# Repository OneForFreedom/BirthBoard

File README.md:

# BirthBoard
A 60% ISO keyboard that has an oled to count down the days to your birthday!

Images + Schematic:

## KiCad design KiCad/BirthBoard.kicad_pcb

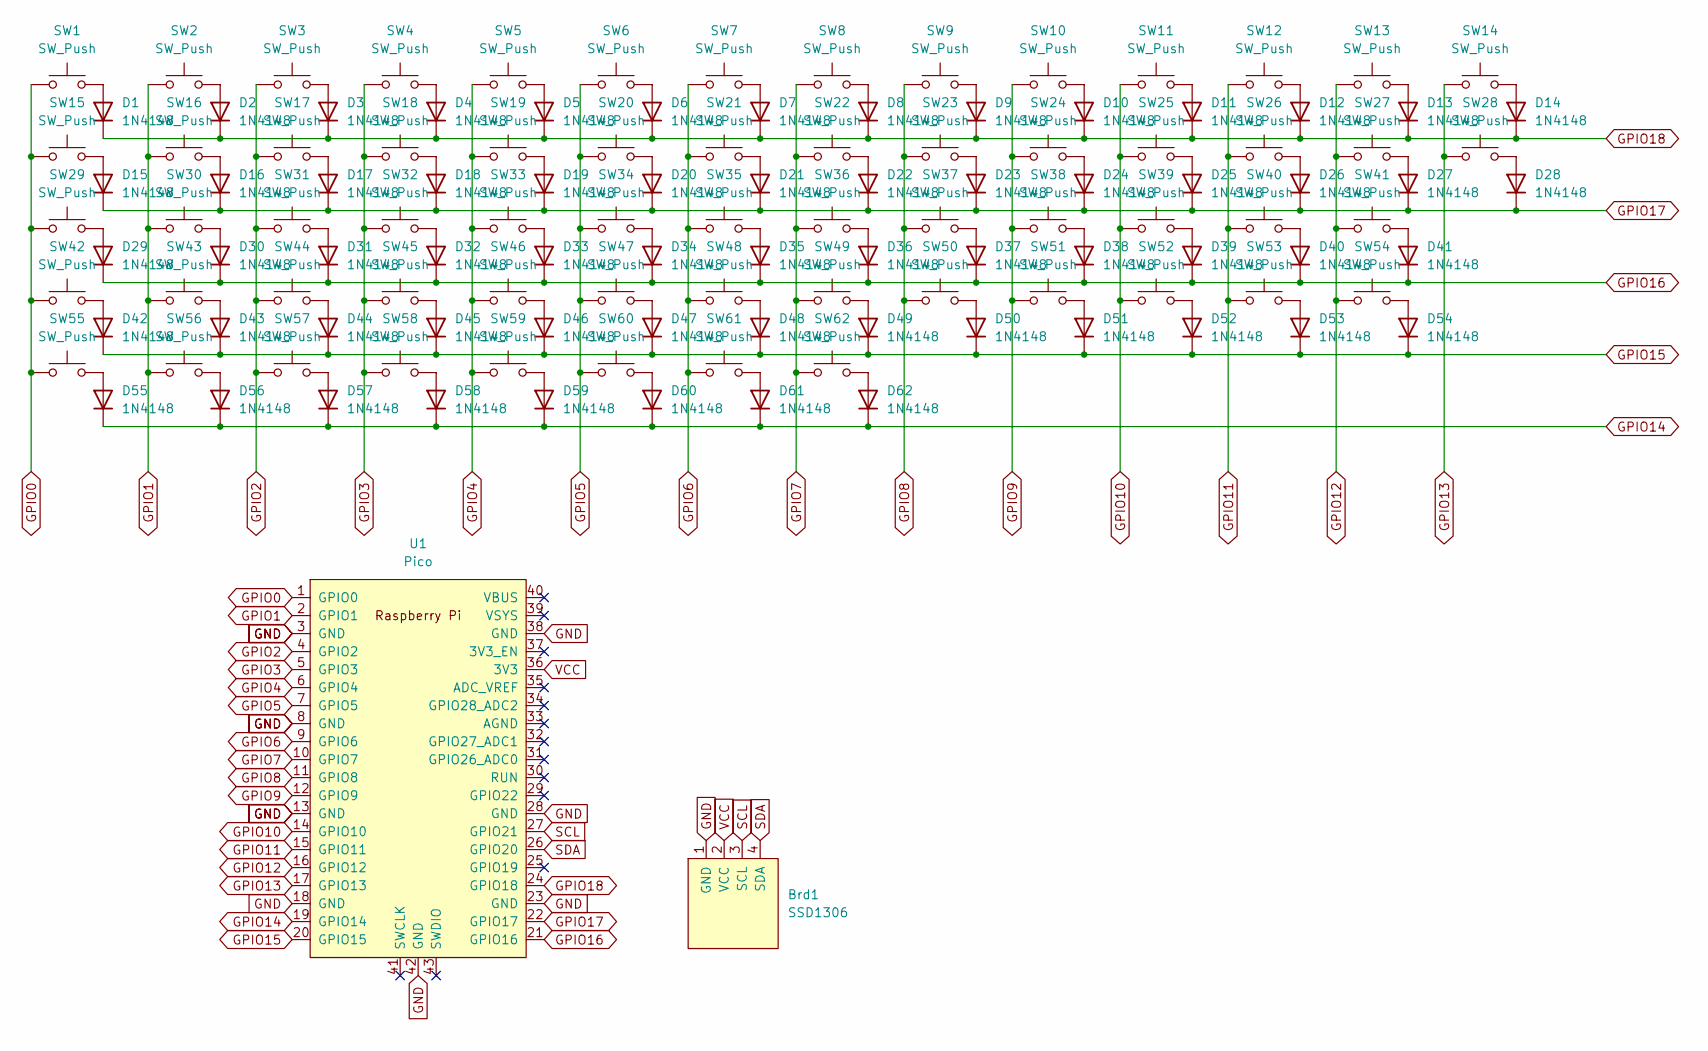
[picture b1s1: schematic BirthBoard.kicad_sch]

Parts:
Brd1: SSD1306; 128x64OLED
D1, D2, D3, D4, D5, D6, D7, D8, D9, D10, D11, D12, D13, D14, D15, D16, D17, D18, D19, D20, D21, D22, D23, D24, D25, D26, D27, D28, D29, D30, D31, D32, D33, D34, D35, D36, D37, D38, D39, D40, D41, D42, D43, D44, D45, D46, D47, D48, D49, D50, D51, D52, D53, D54, D55, D56, D57, D58, D59, D60, D61, D62: 1N4148; D_DO-35_SOD27_P7.62mm_Horizontal
SW1, SW2, SW3, SW4, SW5, SW6, SW7, SW8, SW9, SW10, SW11, SW12, SW13, SW14, SW15, SW16, SW17, SW18, SW19, SW20, SW21, SW22, SW23, SW24, SW25, SW26, SW27, SW28, SW29, SW30, SW31, SW32, SW33, SW34, SW35, SW36, SW37, SW38, SW39, SW40, SW41, SW42, SW43, SW44, SW45, SW46, SW47, SW48, SW49, SW50, SW51, SW52, SW53, SW54, SW55, SW56, SW57, SW58, SW59, SW60, SW61, SW62: SW_Push; SW_Cherry_MX_1.00u_PCB 1
U1: Pico; RPi_Pico_SMD_TH

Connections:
GND: Brd1.1 (GND), U1.3 (GND), U1.8 (GND), U1.13 (GND), U1.18 (GND), U1.23 (GND), U1.28 (GND), U1.38 (GND), U1.42 (GND)
GPIO0: SW1.1, SW15.1, SW29.1, SW42.1, SW55.1, U1.1 (GPIO0)
GPIO1: SW2.1, SW16.1, SW30.1, SW43.1, SW56.1, U1.2 (GPIO1)
GPIO2: SW3.1, SW17.1, SW31.1, SW44.1, SW57.1, U1.4 (GPIO2)
GPIO3: SW4.1, SW18.1, SW32.1, SW45.1, SW58.1, U1.5 (GPIO3)
GPIO4: SW5.1, SW19.1, SW33.1, SW46.1, SW59.1, U1.6 (GPIO4)
GPIO5: SW6.1, SW20.1, SW34.1, SW47.1, SW60.1, U1.7 (GPIO5)
GPIO6: SW7.1, SW21.1, SW35.1, SW48.1, SW61.1, U1.9 (GPIO6)
GPIO7: SW8.1, SW22.1, SW36.1, SW49.1, SW62.1, U1.10 (GPIO7)
GPIO8: SW9.1, SW23.1, SW37.1, SW50.1, U1.11 (GPIO8)
GPIO9: SW10.1, SW24.1, SW38.1, SW51.1, U1.12 (GPIO9)
GPIO10: SW11.1, SW25.1, SW39.1, SW52.1, U1.14 (GPIO10)
GPIO11: SW12.1, SW26.1, SW40.1, SW53.1, U1.15 (GPIO11)
GPIO12: SW13.1, SW27.1, SW41.1, SW54.1, U1.16 (GPIO12)
GPIO13: SW14.1, SW28.1, U1.17 (GPIO13)
GPIO14: D55.1 (K), D56.1 (K), D57.1 (K), D58.1 (K), D59.1 (K), D60.1 (K), D61.1 (K), D62.1 (K), U1.19 (GPIO14)
GPIO15: D42.1 (K), D43.1 (K), D44.1 (K), D45.1 (K), D46.1 (K), D47.1 (K), D48.1 (K), D49.1 (K), D50.1 (K), D51.1 (K), D52.1 (K), D53.1 (K), D54.1 (K), U1.20 (GPIO15)
GPIO16: D29.1 (K), D30.1 (K), D31.1 (K), D32.1 (K), D33.1 (K), D34.1 (K), D35.1 (K), D36.1 (K), D37.1 (K), D38.1 (K), D39.1 (K), D40.1 (K), D41.1 (K), U1.21 (GPIO16)
GPIO17: D15.1 (K), D16.1 (K), D17.1 (K), D18.1 (K), D19.1 (K), D20.1 (K), D21.1 (K), D22.1 (K), D23.1 (K), D24.1 (K), D25.1 (K), D26.1 (K), D27.1 (K), D28.1 (K), U1.22 (GPIO17)
GPIO18: D1.1 (K), D2.1 (K), D3.1 (K), D4.1 (K), D5.1 (K), D6.1 (K), D7.1 (K), D8.1 (K), D9.1 (K), D10.1 (K), D11.1 (K), D12.1 (K), D13.1 (K), D14.1 (K), U1.24 (GPIO18)
unnamed: D1.2 (A), SW1.2
unnamed: D2.2 (A), SW2.2
unnamed: D3.2 (A), SW3.2
unnamed: D4.2 (A), SW4.2
unnamed: D5.2 (A), SW5.2
unnamed: D6.2 (A), SW6.2
unnamed: D7.2 (A), SW7.2
unnamed: D8.2 (A), SW8.2
unnamed: D9.2 (A), SW9.2
unnamed: D10.2 (A), SW10.2
unnamed: D11.2 (A), SW11.2
unnamed: D12.2 (A), SW12.2
unnamed: D13.2 (A), SW13.2
unnamed: D14.2 (A), SW14.2
unnamed: D15.2 (A), SW15.2
unnamed: D16.2 (A), SW16.2
unnamed: D17.2 (A), SW17.2
unnamed: D18.2 (A), SW18.2
unnamed: D19.2 (A), SW19.2
unnamed: D20.2 (A), SW20.2
unnamed: D21.2 (A), SW21.2
unnamed: D22.2 (A), SW22.2
unnamed: D23.2 (A), SW23.2
unnamed: D24.2 (A), SW24.2
unnamed: D25.2 (A), SW25.2
unnamed: D26.2 (A), SW26.2
unnamed: D27.2 (A), SW27.2
unnamed: D28.2 (A), SW28.2
unnamed: D29.2 (A), SW29.2
unnamed: D30.2 (A), SW30.2
unnamed: D31.2 (A), SW31.2
unnamed: D32.2 (A), SW32.2
unnamed: D33.2 (A), SW33.2
unnamed: D34.2 (A), SW34.2
unnamed: D35.2 (A), SW35.2
unnamed: D36.2 (A), SW36.2
unnamed: D37.2 (A), SW37.2
unnamed: D38.2 (A), SW38.2
unnamed: D39.2 (A), SW39.2
unnamed: D40.2 (A), SW40.2
unnamed: D41.2 (A), SW41.2
unnamed: D42.2 (A), SW42.2
unnamed: D43.2 (A), SW43.2
unnamed: D44.2 (A), SW44.2
unnamed: D45.2 (A), SW45.2
unnamed: D46.2 (A), SW46.2
unnamed: D47.2 (A), SW47.2
unnamed: D48.2 (A), SW48.2
unnamed: D49.2 (A), SW49.2
unnamed: D50.2 (A), SW50.2
unnamed: D51.2 (A), SW51.2
unnamed: D52.2 (A), SW52.2
unnamed: D53.2 (A), SW53.2
unnamed: D54.2 (A), SW54.2
unnamed: D55.2 (A), SW55.2
unnamed: D56.2 (A), SW56.2
unnamed: D57.2 (A), SW57.2
unnamed: D58.2 (A), SW58.2
unnamed: D59.2 (A), SW59.2
unnamed: D60.2 (A), SW60.2
unnamed: D61.2 (A), SW61.2
unnamed: D62.2 (A), SW62.2
SCL: Brd1.3 (SCL), U1.27 (GPIO21)
SDA: Brd1.4 (SDA), U1.26 (GPIO20)
VCC: Brd1.2 (VCC), U1.36 (3V3)

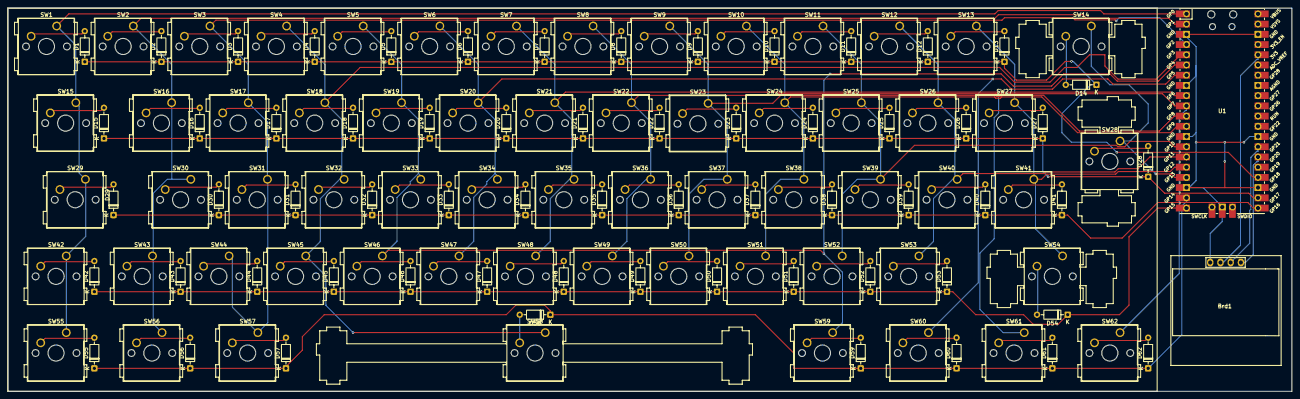
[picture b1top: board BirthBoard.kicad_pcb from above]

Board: 2 copper layers, 319.1 x 95.2 mm, 126 parts (0 on the bottom side), 85 nets.

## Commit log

2025-08-14 Create LICENSE
2025-08-14 Rename BirthBoard.ino to Firmware/BirthBoard.ino
2025-08-14 Rename BirthBoard.zip to Gerbers/BirthBoard.zip
2025-08-14 Rename BirthBoard Full.step to Cad/BirthBoard Full.step
2025-08-14 Rename Screenshot 2025-08-14 160025.png to 3DB
2025-08-14 Rename 3DB to 3DB.png
2025-08-14 Rename Screenshot 2025-08-14 201052.png to 3DFM.png
2025-08-14 Rename Screenshot 2025-08-14 201059.png to 3DFF.png
2025-08-14 Rename Screenshot 2025-08-15 001125.png to 3DD.png
2025-08-14 Rename Screenshot 2025-08-15 005033.png to 3DS.png
2025-08-14 Rename Screenshot 2025-08-15 005056.png to 3DF.png
2025-08-15 Rename Screenshot 2025-08-15 005104.png to 3DSM.png
2025-08-15 Rename Screenshot 2025-08-15 005125.png to 3DSR.png
2025-08-15 Rename Screenshot 2025-08-15 005146.png to 3DSCU.png
2025-08-15 Rename Screenshot 2025-08-15 005158.png to 3DT.png
2025-08-15 Rename Screenshot 2025-08-15 005530.png to Schematic.png
2025-08-15 Rename Screenshot 2025-08-15 005549.png to PCB.png
2025-08-30 Rename BirthBoard.kicad_prl to KiCad/BirthBoard.kicad_prl
